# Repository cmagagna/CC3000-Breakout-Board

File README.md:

<h3>This project is abandoned!</h3>

<p>
I've given up on the CC3000, it's just too buggy and problematic.
</p>

<p>TI themselves say this on the CC3000 page:</p>

<pre>
TI recommends CC3200 & CC3100 for all new and existing embedded Wi-Fi & Internet of Things applications.
</pre>

<p>And they've removed references to the CC3000 on their SimpleLink WiFi page at
<a href="http://www.ti.com/ww/en/simplelink_embedded_wi-fi/home.html">http://www.ti.com/ww/en/simplelink_embedded_wi-fi/home.html</a>
</p>

<p>
I'm going to leave these pages here so people searching the web for help don't find dead links,
but I recommend you abandon your quest to make this half-baked module work. Best of luck to you.
</p>

<hr/>
<hr/>
<hr/>

CC3000 Breakout
=============

<p>Version 1.4</p>

<p>Yet another breakout board for the TI CC3000 WiFi module</p>

<p>Based on a design & library by Matt Bigarani, http://www.centerblack.com</p>

<p>This design is licensed under the Creative Commons CC by NC SA (http://creativecommons.org/licenses/by-nc-sa/3.0/us/). OK to share & remix for any noncommercial purpose</p>

<p>The antenna used by Matt from the SparkFun-RF library was the wrong size. SparkFun had one that was close (ANTENNA-CHIP5) but wasn't exactly right so I modified the part in their library. The modified library is included in this project as SparkFun-RF-Modified.lbr</p>
 
<p>Changes:</p>
<ul>
<li>1.4 - Changed antenna trace from 20 mil to 50 mil & antenna trace gap from 12 mil to 10 mil based on calculations from http://chemandy.com/calculators/coplanar-waveguide-with-ground-calculator.htm</li>
<li>1.3 - First board design to be manufactured. Fixed antenna footprint from V1.2</li>
<li>1.2 - Fixed antenna gap per antenna datasheet</li>
<li>1.1 - Revised BOM to use the same parts as TI whenever possible</li>
<li>1.0 - Initial prototype</li>
</ul>

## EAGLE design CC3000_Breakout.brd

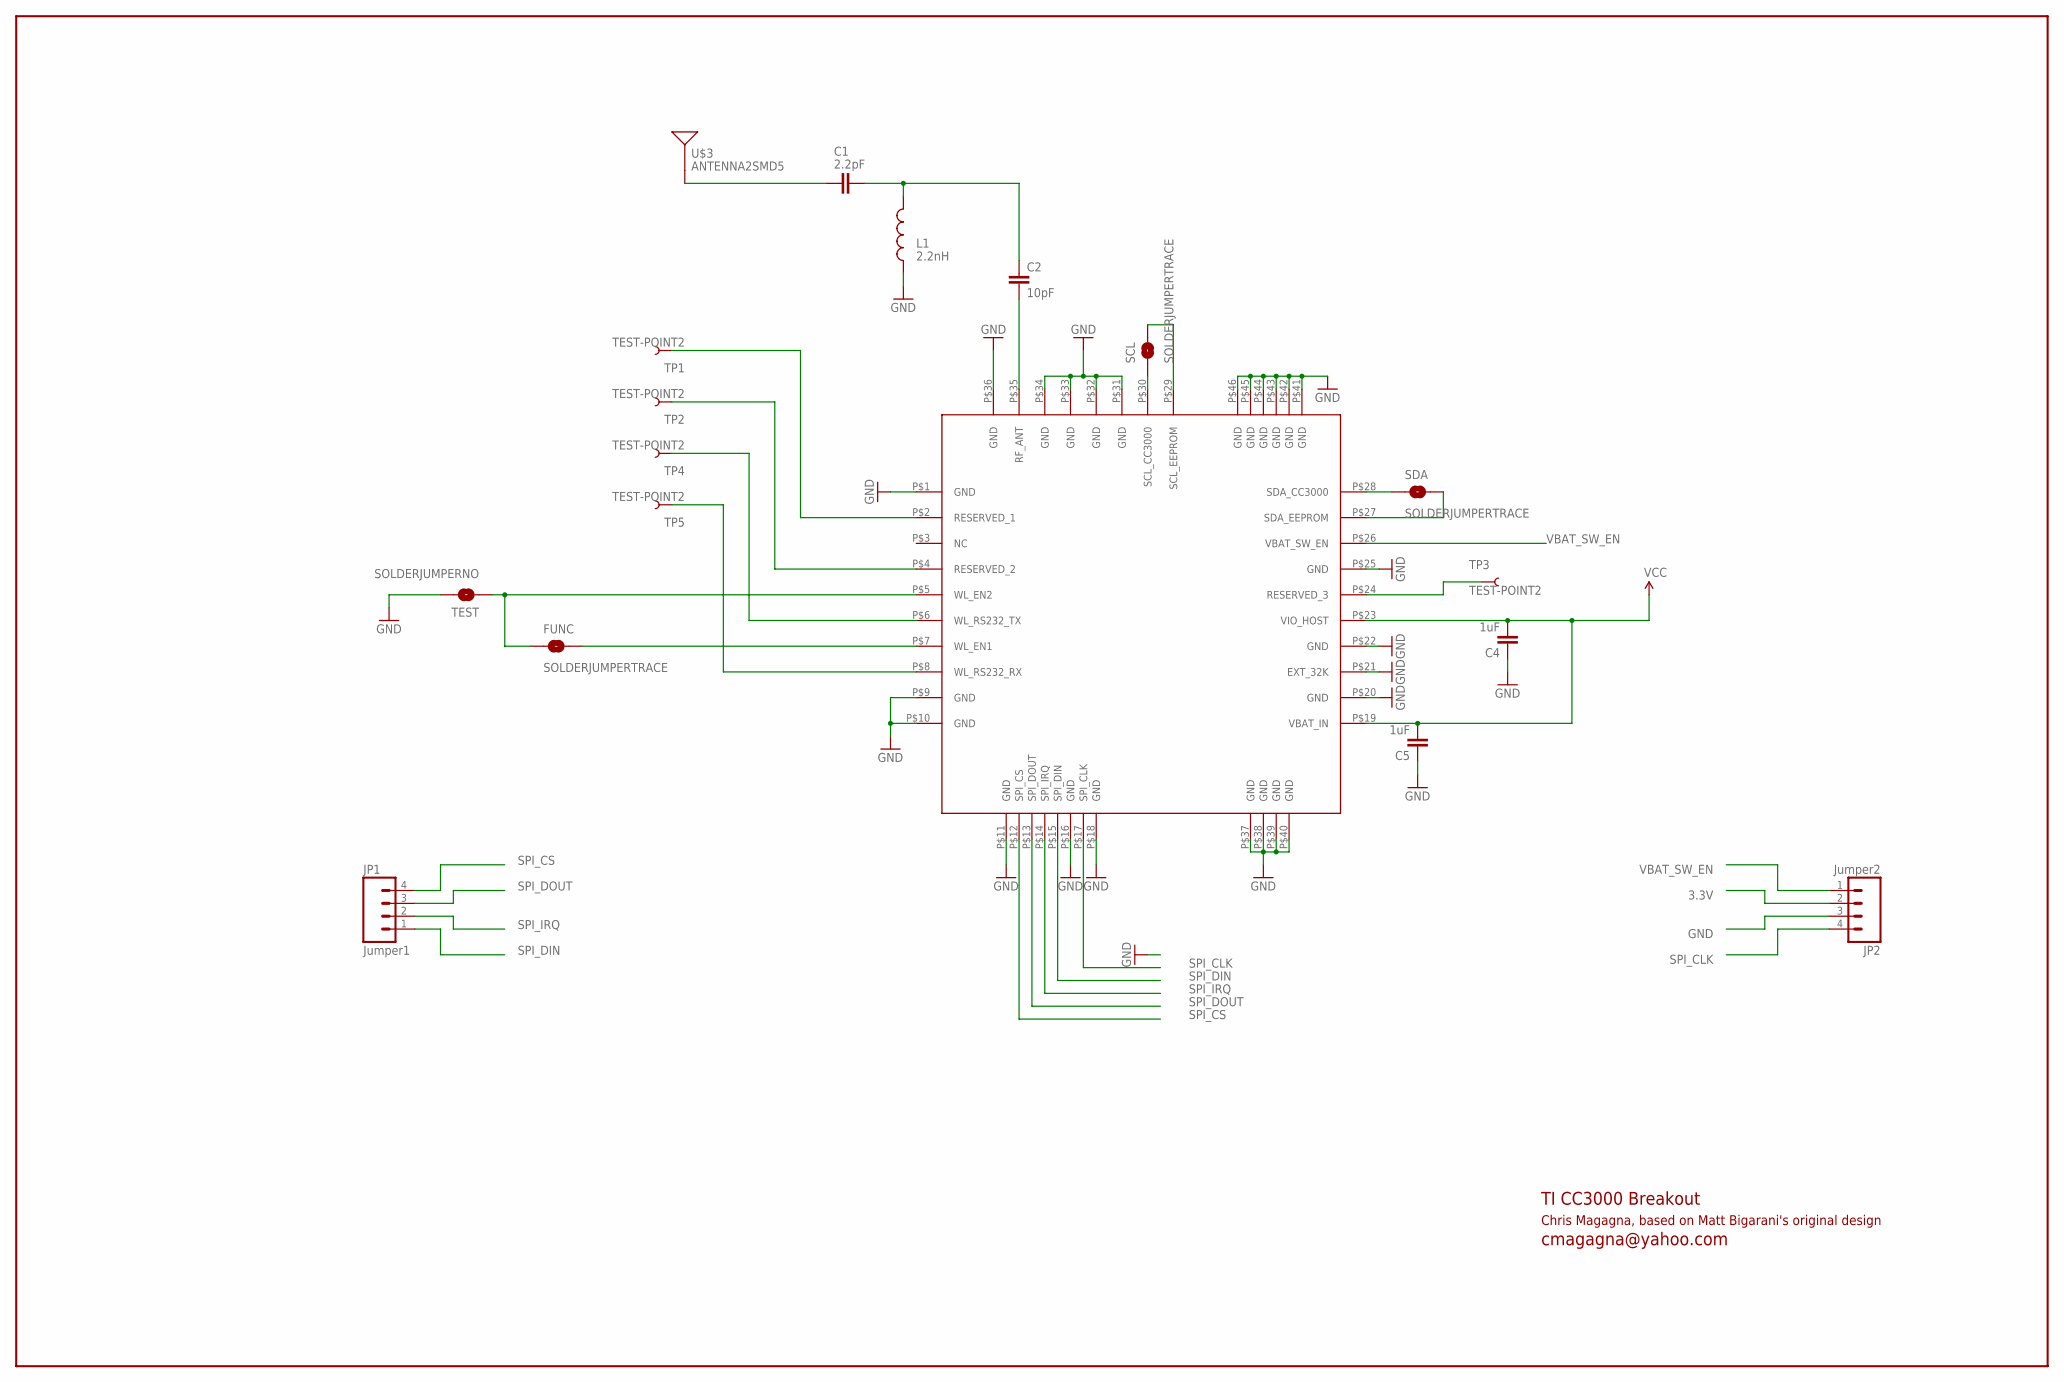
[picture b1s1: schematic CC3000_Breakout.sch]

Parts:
C1: 2.2pF; 0402-CAP
C2: 10pF; 0402-CAP
C4, C5: 1uF; 0402-CAP
FUNC: SOLDERJUMPERTRACE; SJ_2S-TRACE
JP1: Jumper1; 1X04
JP2: Jumper2; 1X04
L1: 2.2nH; C0402
SCL: SOLDERJUMPERTRACE; SJ_2S-TRACE
SDA: SOLDERJUMPERTRACE; SJ_2S-TRACE
TEST: SOLDERJUMPERNO; SJ_2S-NO
TP1, TP2, TP3, TP4, TP5: TEST-POINT2; PAD.02X.02
U$1: CC3000
U$3: ANTENNA2SMD5; ANTENNA-CHIP5

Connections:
3.3V: C4.2, C5.2, JP2.2, U$1.P$19 (VBAT_IN), U$1.P$23 (VIO_HOST)
GND: C4.1, C5.1, JP2.3, L1.1, TEST.2, U$1.P$1 (GND), U$1.P$9 (GND), U$1.P$10 (GND), U$1.P$11 (GND), U$1.P$16 (GND), U$1.P$18 (GND), U$1.P$20 (GND), U$1.P$21 (EXT_32K), U$1.P$22 (GND), U$1.P$25 (GND), U$1.P$31 (GND), U$1.P$32 (GND), U$1.P$33 (GND), U$1.P$34 (GND), U$1.P$36 (GND), U$1.P$37 (GND), U$1.P$38 (GND), U$1.P$39 (GND), U$1.P$40 (GND), U$1.P$41 (GND), U$1.P$42 (GND), U$1.P$43 (GND), U$1.P$44 (GND), U$1.P$45 (GND), U$1.P$46 (GND)
unnamed: FUNC.2, U$1.P$7 (WL_EN1)
unnamed: FUNC.1, TEST.1, U$1.P$5 (WL_EN2)
unnamed: TP1.P$1, U$1.P$2 (RESERVED_1)
unnamed: TP2.P$1, U$1.P$4 (RESERVED_2)
unnamed: TP4.P$1, U$1.P$6 (WL_RS232_TX)
unnamed: TP5.P$1, U$1.P$8 (WL_RS232_RX)
unnamed: TP3.P$1, U$1.P$24 (RESERVED_3)
unnamed: C1.2, C2.1, L1.2
unnamed: C2.2, U$1.P$35 (RF_ANT)
unnamed: SCL.1, U$1.P$30 (SCL_CC3000)
unnamed: C1.1, U$3.FEED
unnamed: SCL.2, U$1.P$29 (SCL_EEPROM)
unnamed: SDA.1, U$1.P$28 (SDA_CC3000)
unnamed: SDA.2, U$1.P$27 (SDA_EEPROM)
SPI_CLK: JP2.4, U$1.P$17 (SPI_CLK)
SPI_CS: JP1.4, U$1.P$12 (SPI_CS)
SPI_DIN: JP1.1, U$1.P$15 (SPI_DIN)
SPI_DOUT: JP1.3, U$1.P$13 (SPI_DOUT)
SPI_IRQ: JP1.2, U$1.P$14 (SPI_IRQ)
VBAT_SW_EN: JP2.1, U$1.P$26 (VBAT_SW_EN)

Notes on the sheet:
Chris Magagna, based on Matt Bigarani's original design
cmagagna@yahoo.com
TI CC3000 Breakout

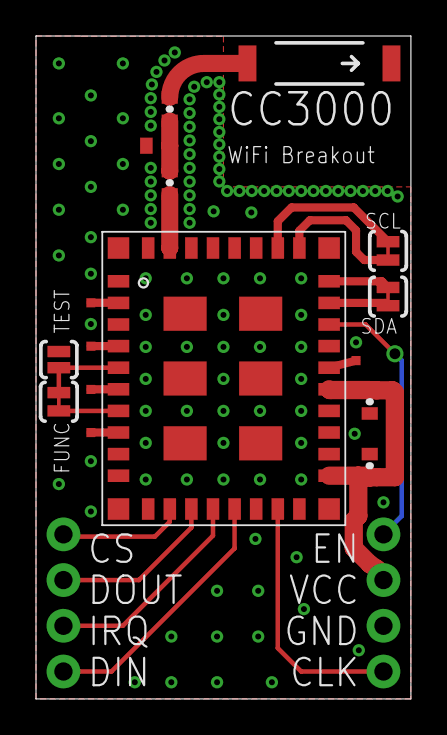
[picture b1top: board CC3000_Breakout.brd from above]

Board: 2 copper layers, 20.8 x 36.8 mm, 18 parts (0 on the bottom side), 22 nets.

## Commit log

2013-07-14 Version 1.0.1
    Initial upload
2013-07-14 Added BOM
2013-07-14 Added BOM and license
2013-07-14 Version 1.1
    Removed 2nd (NL) inductor, straightened out antenna trace
2013-07-15 Version 1.2
    Changed antenna trace width from 14.4 mil to 20 mil, reworked via
    stitching around antenna gap
2013-07-15 Version 1.3
    The antenna in Matt's design wasn't the right size, I've fixed the
    antenna footprint to match the actual chip used.
2014-08-05 Abandoned project!

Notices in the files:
CC3000_Breakout.brd:
(C)2013 Bubbletronics
parts and their libraries:
SparkFun-Passives: Licensing: CC v3.0 Share-Alike You are welcome to use this library for commercial purposes.
